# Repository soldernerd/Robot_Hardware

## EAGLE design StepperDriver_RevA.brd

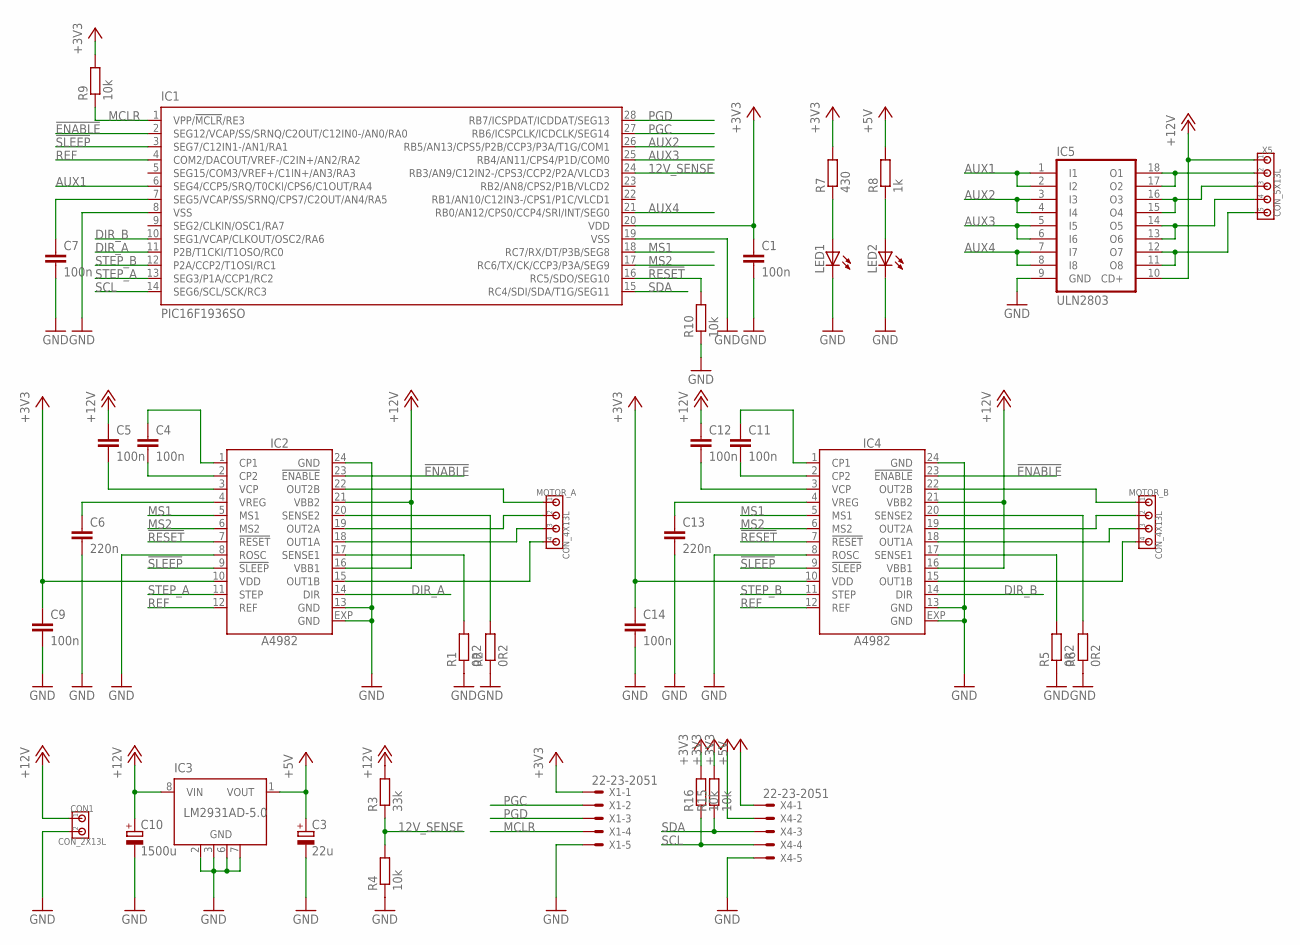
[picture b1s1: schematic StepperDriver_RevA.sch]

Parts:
C1, C4, C5, C7, C9, C11, C12, C14: 100n; C0805
C3: 22u; SMC_C
C6, C13: 220n; C0805
C10: 1500u; 10MM
CON1: CON_2X13L; 200MIL_2X
IC1: PIC16F1936SO; SO28W
IC2, IC4: A4982; TSSOP-24_LP
IC3: LM2931AD-5.0; SO8
IC5: ULN2803; SO18W
LED1, LED2: LED0805
MOTOR_A: CON_4X13L; 200MIL_4X
MOTOR_B: CON_4X13L; 200MIL_4X
R1, R2, R5, R6: 0R2; 0612
R3: 33k; R0805
R4, R9, R10, R15, R16: 10k; R0805
R7: 430; R0805
R8: 1k; R0805
X1, X4: 22-23-2051
X5: CON_5X13L; 200MIL_5X

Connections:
12V_SENSE: IC1.24 (RB3/AN9/C12IN2-/CPS3/CCP2/P2A/VLCD3), R3.1, R4.2
!ENABLE!: IC1.2 (SEG12/VCAP/SS/SRNQ/C2OUT/C12IN0-/AN0/RA0), IC2.23 (!ENABLE!), IC4.23 (!ENABLE!)
!RESET!: IC1.16 (RC5/SDO/SEG10), IC2.7 (!RESET!), IC4.7 (!RESET!), R10.2
!SLEEP!: IC1.3 (SEG7/C12IN1-/AN1/RA1), IC2.9 (!SLEEP!), IC4.9 (!SLEEP!)
+3V3: C1.1, C9.1, C14.1, IC1.20 (VDD), IC2.10 (VDD), IC4.10 (VDD), R7.2, R9.2, R15.2, R16.2, X1.1, X4.2
+5V: C3.+, IC3.1 (VOUT), R8.2, X4.1
+12V: C5.1, C10.+, C12.1, CON1.1, IC2.16 (VBB1), IC2.21 (VBB2), IC3.8 (VIN), IC4.16 (VBB1), IC4.21 (VBB2), IC5.10 (CD+), R3.2, X5.1
AUX1: IC1.6 (SEG4/CCP5/SRQ/T0CKI/CPS6/C1OUT/RA4), IC5.1 (I1), IC5.2 (I2)
AUX2: IC1.26 (RB5/AN13/CPS5/P2B/CCP3/P3A/T1G/COM1), IC5.3 (I3), IC5.4 (I4)
AUX3: IC1.25 (RB4/AN11/CPS4/P1D/COM0), IC5.5 (I5), IC5.6 (I6)
AUX4: IC1.21 (RB0/AN12/CPS0/CCP4/SRI/INT/SEG0), IC5.7 (I7), IC5.8 (I8)
DIR_A: IC1.11 (P2B/T1CKI/T1OSO/RC0), IC2.14 (DIR)
DIR_B: IC1.10 (SEG1/VCAP/CLKOUT/OSC2/RA6), IC4.14 (DIR)
GND: C1.2, C3.-, C6.2, C7.2, C9.2, C10.-, C13.2, C14.2, CON1.2, IC1.8 (VSS), IC1.19 (VSS), IC2.8 (ROSC), IC2.13 (GND), IC2.24 (GND), IC2.EXP (GND), IC3.2 (GND), IC3.3 (GND), IC3.6 (GND), IC3.7 (GND), IC4.8 (ROSC), IC4.13 (GND), IC4.24 (GND), IC4.EXP (GND), IC5.9 (GND), LED1.C, LED2.C, R1.1, R2.1, R4.1, R5.1, R6.1, R10.1, X1.5, X4.5
MCLR: IC1.1 (VPP/!MCLR!/RE3), R9.1, X1.4
MS1: IC1.18 (RC7/RX/DT/P3B/SEG8), IC2.5 (MS1), IC4.5 (MS1)
MS2: IC1.17 (RC6/TX/CK/CCP3/P3A/SEG9), IC2.6 (MS2), IC4.6 (MS2)
unnamed: LED1.A, R7.1
unnamed: LED2.A, R8.1
unnamed: C7.1, IC1.7 (SEG5/VCAP/SS/SRNQ/CPS7/C2OUT/AN4/RA5)
unnamed: IC2.22 (OUT2B), MOTOR_A.1
unnamed: IC2.19 (OUT2A), MOTOR_A.2
unnamed: IC2.18 (OUT1A), MOTOR_A.3
unnamed: C4.2, IC2.2 (CP2)
unnamed: IC2.15 (OUT1B), MOTOR_A.4
unnamed: C4.1, IC2.1 (CP1)
unnamed: C5.2, IC2.3 (VCP)
unnamed: C6.1, IC2.4 (VREG)
unnamed: IC2.20 (SENSE2), R2.2
unnamed: IC2.17 (SENSE1), R1.2
unnamed: IC4.22 (OUT2B), MOTOR_B.1
unnamed: IC4.19 (OUT2A), MOTOR_B.2
unnamed: IC4.18 (OUT1A), MOTOR_B.3
unnamed: IC4.15 (OUT1B), MOTOR_B.4
unnamed: C11.2, IC4.2 (CP2)
unnamed: C11.1, IC4.1 (CP1)
unnamed: C12.2, IC4.3 (VCP)
unnamed: C13.1, IC4.4 (VREG)
unnamed: IC4.20 (SENSE2), R6.2
unnamed: IC4.17 (SENSE1), R5.2
unnamed: IC5.17 (O2), IC5.18 (O1), X5.2
unnamed: IC5.15 (O4), IC5.16 (O3), X5.3
unnamed: IC5.13 (O6), IC5.14 (O5), X5.4
unnamed: IC5.11 (O8), IC5.12 (O7), X5.5
PGC: IC1.27 (RB6/ICSPCLK/ICDCLK/SEG14), X1.2
PGD: IC1.28 (RB7/ICSPDAT/ICDDAT/SEG13), X1.3
REF: IC1.4 (COM2/DACOUT/VREF-/C2IN+/AN2/RA2), IC2.12 (REF), IC4.12 (REF)
SCL: IC1.14 (SEG6/SCL/SCK/RC3), R16.1, X4.4
SDA: IC1.15 (RC4/SDI/SDA/T1G/SEG11), R15.1, X4.3
STEP_A: IC1.13 (SEG3/P1A/CCP1/RC2), IC2.11 (STEP)
STEP_B: IC1.12 (P2A/CCP2/T1OSI/RC1), IC4.11 (STEP)

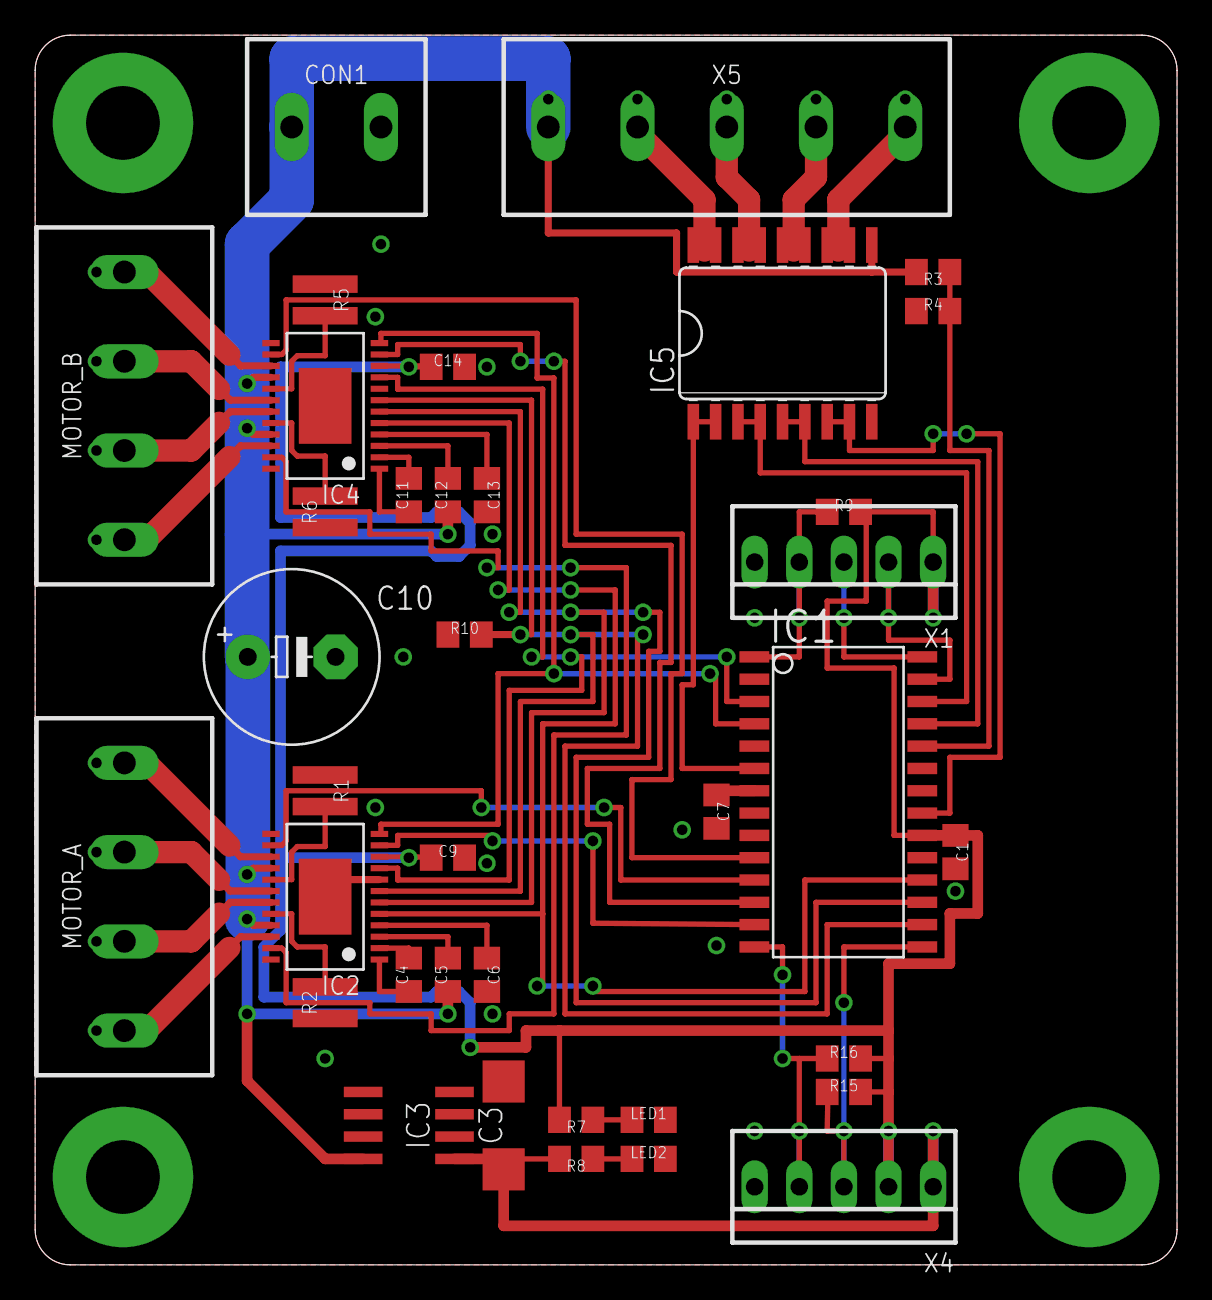
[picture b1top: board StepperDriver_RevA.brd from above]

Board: 2 copper layers, 65.0 x 70.0 mm, 37 parts (0 on the bottom side), 51 nets.
